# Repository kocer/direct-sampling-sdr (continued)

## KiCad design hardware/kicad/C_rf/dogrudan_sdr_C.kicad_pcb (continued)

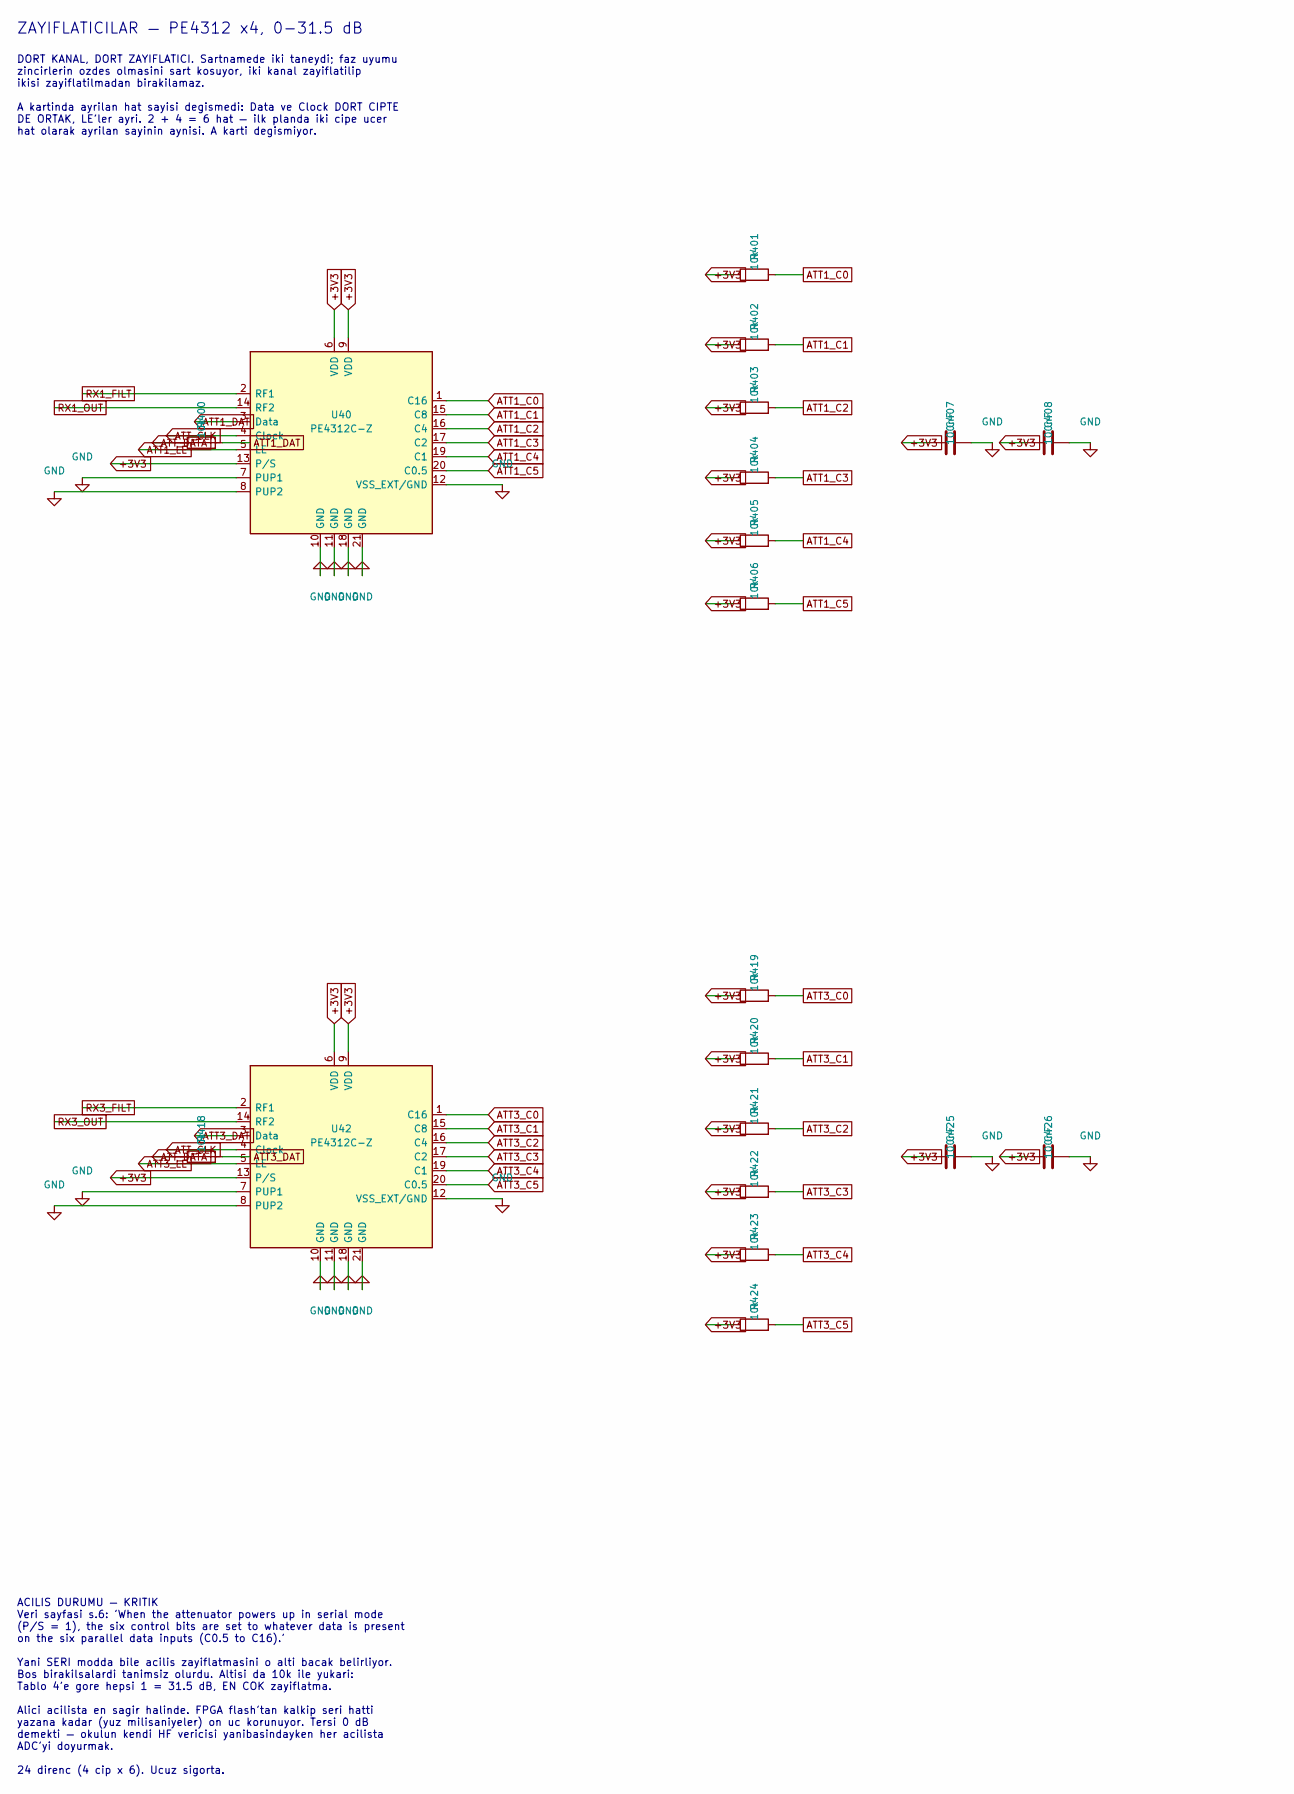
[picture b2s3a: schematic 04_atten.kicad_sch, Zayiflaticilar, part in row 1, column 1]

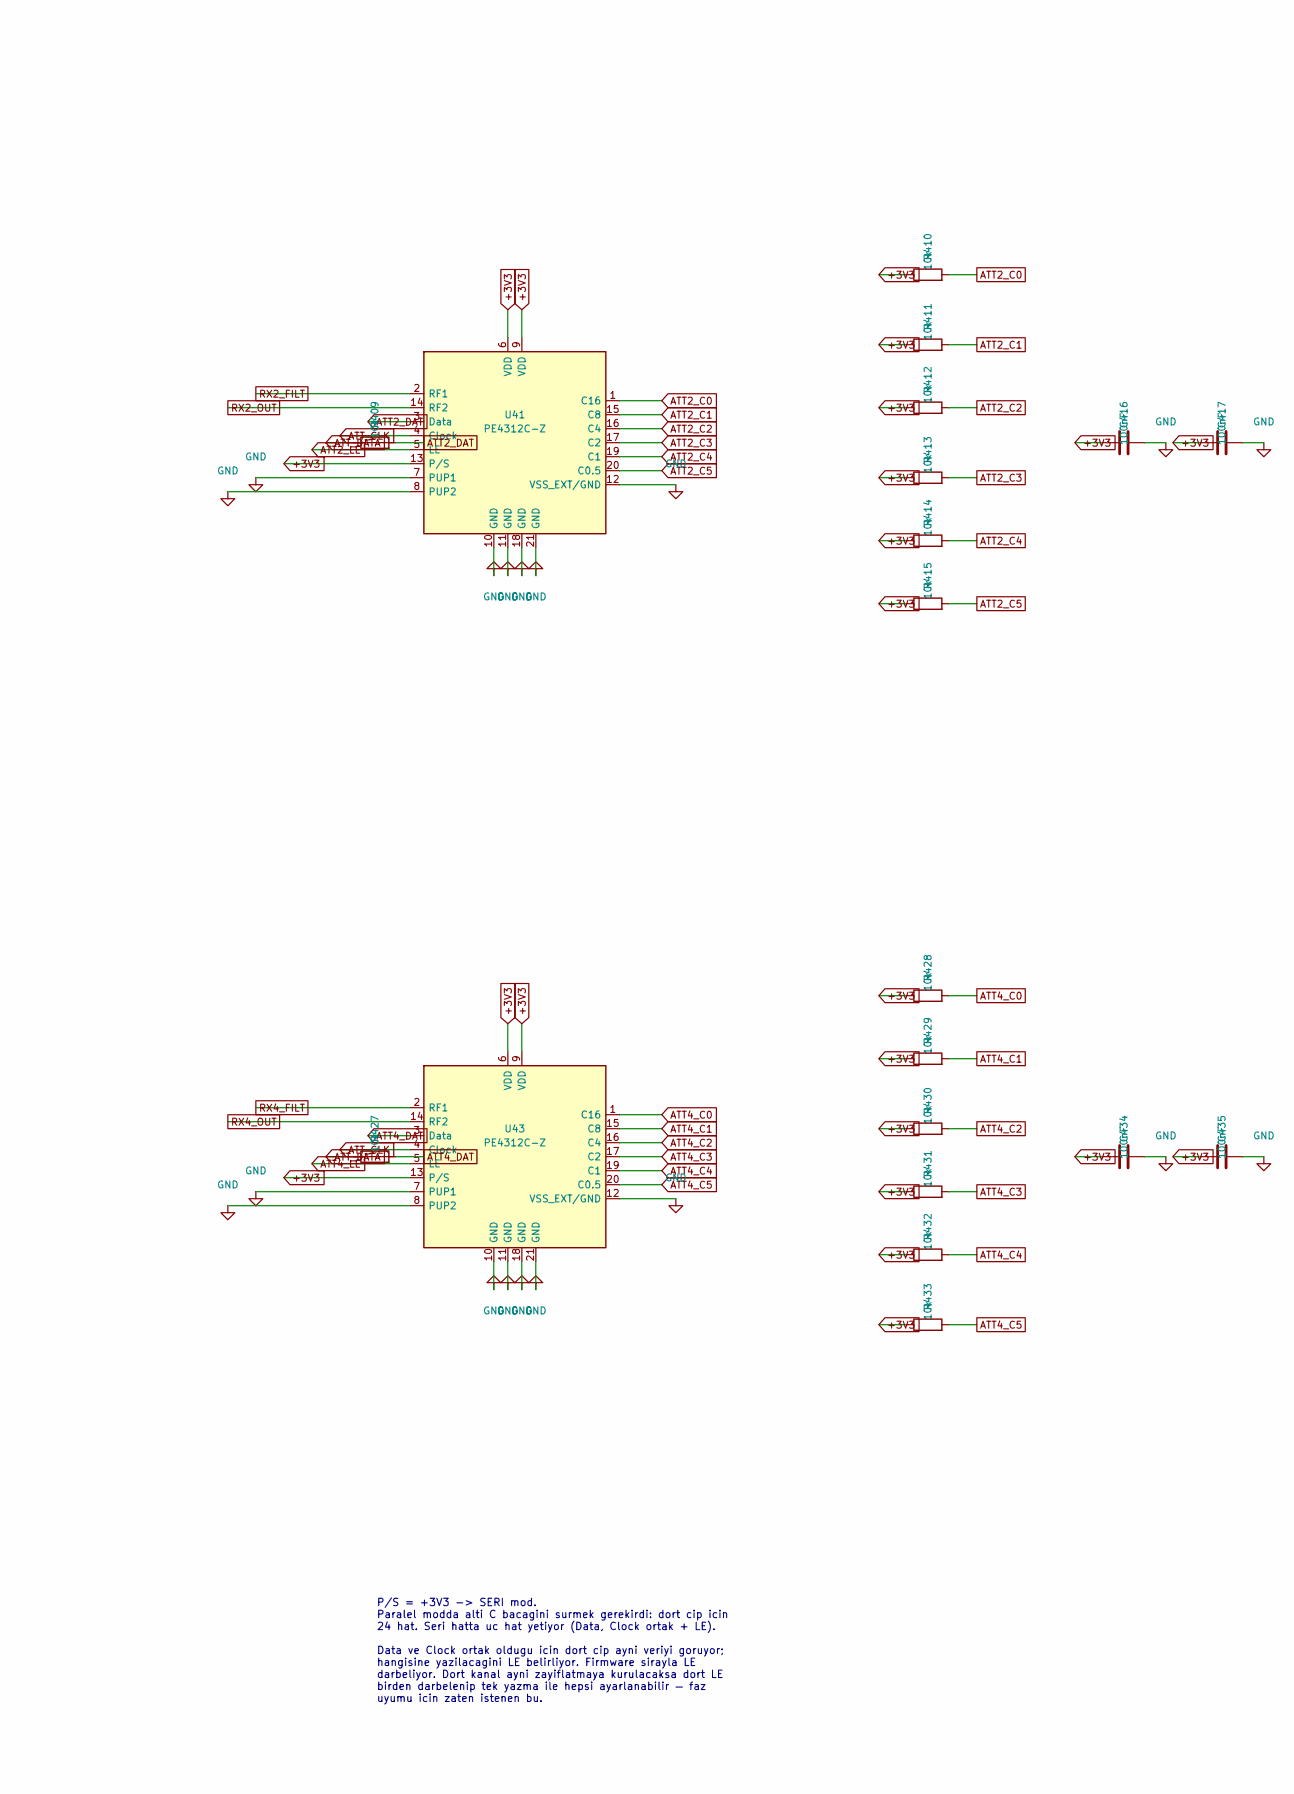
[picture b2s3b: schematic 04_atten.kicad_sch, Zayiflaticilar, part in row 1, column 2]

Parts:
C407, C408, C416, C417, C425, C426, C434, C435: 100nF; C_0402_1005Metric
R400, R401, R402, R403, R404, R405, R406, R409, R410, R411, R412, R413, R414, R415, R418, R419, R420, R421, R422, R423, R424, R427, R428, R429, R430, R431, R432, R433: 10k; R_0603_1608Metric
U40, U41, U42, U43: PE4312C-Z; TQFN-20-1EP_4x4mm_P0.5mm_EP2.1x2.1mm

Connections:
+3V3: C407.1, C408.1, C416.1, C417.1, C425.1, C426.1, C434.1, C435.1, R401.1, R402.1, R403.1, R404.1, R405.1, R406.1, R410.1, R411.1, R412.1, R413.1, R414.1, R415.1, R419.1, R420.1, R421.1, R422.1, R423.1, R424.1, R428.1, R429.1, R430.1, R431.1, R432.1, R433.1, U40.6 (VDD), U40.9 (VDD), U40.13 (P/S), U41.6 (VDD), U41.9 (VDD), U41.13 (P/S), U42.6 (VDD), U42.9 (VDD), U42.13 (P/S), U43.6 (VDD), U43.9 (VDD), U43.13 (P/S); also elsewhere on the board
ATT1_C0: R401.2, U40.1 (C16)
ATT1_C1: R402.2, U40.15 (C8)
ATT1_C2: R403.2, U40.16 (C4)
ATT1_C3: R404.2, U40.17 (C2)
ATT1_C4: R405.2, U40.19 (C1)
ATT1_C5: R406.2, U40.20 (C0.5)
ATT1_DAT: R400.2, U40.3 (Data)
ATT1_LE: U40.5 (LE); also elsewhere on the board
ATT2_C0: R410.2, U41.1 (C16)
ATT2_C1: R411.2, U41.15 (C8)
ATT2_C2: R412.2, U41.16 (C4)
ATT2_C3: R413.2, U41.17 (C2)
ATT2_C4: R414.2, U41.19 (C1)
ATT2_C5: R415.2, U41.20 (C0.5)
ATT2_DAT: R409.2, U41.3 (Data)
ATT2_LE: U41.5 (LE); also elsewhere on the board
ATT3_C0: R419.2, U42.1 (C16)
ATT3_C1: R420.2, U42.15 (C8)
ATT3_C2: R421.2, U42.16 (C4)
ATT3_C3: R422.2, U42.17 (C2)
ATT3_C4: R423.2, U42.19 (C1)
ATT3_C5: R424.2, U42.20 (C0.5)
ATT3_DAT: R418.2, U42.3 (Data)
ATT3_LE: U42.5 (LE); also elsewhere on the board
ATT4_C0: R428.2, U43.1 (C16)
ATT4_C1: R429.2, U43.15 (C8)
ATT4_C2: R430.2, U43.16 (C4)
ATT4_C3: R431.2, U43.17 (C2)
ATT4_C4: R432.2, U43.19 (C1)
ATT4_C5: R433.2, U43.20 (C0.5)
ATT4_DAT: R427.2, U43.3 (Data)
ATT4_LE: U43.5 (LE); also elsewhere on the board
ATT_CLK: U40.4 (Clock), U41.4 (Clock), U42.4 (Clock), U43.4 (Clock); also elsewhere on the board
ATT_DATA: R400.1, R409.1, R418.1, R427.1; also elsewhere on the board
RX1_FILT: U40.2 (RF1); also elsewhere on the board
RX1_OUT: U40.14 (RF2); also elsewhere on the board
RX2_FILT: U41.2 (RF1); also elsewhere on the board
RX2_OUT: U41.14 (RF2); also elsewhere on the board
RX3_FILT: U42.2 (RF1); also elsewhere on the board
RX3_OUT: U42.14 (RF2); also elsewhere on the board
RX4_FILT: U43.2 (RF1); also elsewhere on the board
RX4_OUT: U43.14 (RF2); also elsewhere on the board

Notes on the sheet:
ZAYIFLATICILAR — PE4312 x4, 0-31.5 dB
P/S = +3V3 -> SERI mod. Paralel modda alti C bacagini surmek gerekirdi: dort cip icin 24 hat. Seri hatta uc hat yetiyor (Data, Clock ortak + LE). Data ve Clock ortak oldugu icin dort cip ayni veriyi goruyor; hangisine yazilacagini LE belirliyor. Firmware sirayla LE darbeliyor. Dort kanal ayni zayif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
ACILIS DURUMU — KRITIK Veri sayfasi s.6: 'When the attenuator powers up in serial mode (P/S = 1), the six control bits are set to whatever data is present on the six parallel data inputs (C0.5 to C16).' Yani SERI modda bile acilis zayiflatmasini o alti bacak belirliyor. Bos birakilsalardi tanimsiz 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
DORT KANAL, DORT ZAYIFLATICI. Sartnamede iki taneydi; faz uyumu zincirlerin ozdes olmasini sart kosuyor, iki kanal zayiflatilip ikisi zayiflatilmadan birakilamaz. A kartinda ayrilan hat sayisi degismedi: Data ve Clock DORT CIPTE DE ORTAK, LE'ler ayri. 2 + 4 = 6 hat — ilk planda iki cipe ucer hat ol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

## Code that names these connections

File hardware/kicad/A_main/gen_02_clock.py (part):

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# ================================================================== VCXO
s.text("VCXO — ABLNO-V, 80.000 MHz", 16, 40, 1.6)
s.sym(X, "Y10", "ABLNO-V-80.000MHZ", 55, 70, fp=FX)
s.pin_label(X, "1", 55, 70, 0, "VCXO_VC", "input", d=10.16)
s.pin_label(X, "4", 55, 70, 0, "VCXO_VDD", "input", d=10.16)
s.pin_label(X, "3", 55, 70, 0, "CLK80", "output", d=10.16)
s.pin_power(X, "2", 55, 70, 0, "GND", d=7.62)
# VCXO beslemesi ferritten geciyor, ferrit pasif: ERC bu rayda bir
# guc kaynagi goremiyor. Bayrak, gercek baglanti degil.
s.glabel("VCXO_VDD", 30, 40, "input")
s.wire(30, 40, 30, 33.65)
s.pwr_flag(30, 33.65)

# ferrit + ayristirma: besleme gurultusu DOGRUDAN faz gurultusu
s.sym(L, "FB10", "ferrit 600R", 55, 40, rot=90, fp=FFB)
s.pin_label(L, "1", 55, 40, 90, "+3V3_CLK", "input")
s.pin_label(L, "2", 55, 40, 90, "VCXO_VDD", "output")
for i, v in enumerate(("100nF", "10uF")):
    s.sym(C, cnt("C"), v, 95 + i * 20, 45, rot=90, fp=FC)
    s.pin_label(C, "1", 95 + i * 20, 45, 90, "VCXO_VDD", "passive")
    s.pin_power(C, "2", 95 + i * 20, 45, 90, "GND")

s.text("Besleme gurultusu DOGRUDAN faz gurultusune donusuyor.\\n"
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
# 3.3 V CMOS cikisi 1.8 V p-p sinira indiriliyor
s.sym(R, "R210", "220R", 60, 145, rot=90, fp=FR)
s.pin_label(R, "1", 60, 145, 90, "CLK80", "passive")
s.pin_label(R, "2", 60, 145, 90, "CLK80_DIV", "passive")
s.sym(R, "R211", "100R", 85, 158, rot=90, fp=FR)
s.pin_label(R, "1", 85, 158, 90, "CLK80_DIV", "passive")
s.pin_power(R, "2", 85, 158, 90, "GND")

s.sym(C, "C210", "100nF", 110, 145, rot=90, fp=FC)
s.pin_label(C, "1", 110, 145, 90, "CLK80_DIV", "passive")
s.pin_label(C, "2", 110, 145, 90, "BUFCLK_P", "passive")
s.sym(C, "C211", "100nF", 110, 170, rot=90, fp=FC)
s.pin_label(C, "1", 110, 170, 90, "BUFCLK_N", "passive")
s.pin_power(C, "2", 110, 170, 90, "GND")

# her iki giris VREF'e (VS/2 = 0.9 V) 1k ile bias
for i, net in enumerate(("BUFCLK_P", "BUFCLK_N")):
    s.sym(R, f"R{212 + i}", "1k", 145, 145 + i * 25, rot=90, fp=FR)
    s.pin_label(R, "1", 145, 145 + i * 25, 90, "CLK_VREF", "passive")
    s.pin_label(R, "2", 145, 145 + i * 25, 90, net, "passive")
s.sym(C, "C212", "100nF", 175, 158, rot=90, fp=FC)
s.pin_label(C, "1", 175, 158, 90, "CLK_VREF", "passive")
s.pin_power(C, "2", 175, 158, 90, "GND")

s.text("** BU BOLUM ILK PLANDA YOKTU. ** VCXO cikisi 3.3 V LVCMOS,\\n"
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s.text("ADCLK846 — 1:6 LVDS", 300, 40, 2.0)
BX, BY = 340, 110
s.sym(B, "U15", "ADCLK846BCPZ", BX, BY, fp=FB, unit=1)
s.pin_label(B, "3", BX, BY, 0, "BUFCLK_P", "input", d=10.16)
s.pin_label(B, "2", BX, BY, 0, "BUFCLK_N", "input", d=15.24)
s.pin_label(B, "1", BX, BY, 0, "CLK_VREF", "output", d=20.32)
s.pin_power(B, "5", BX, BY, 0, "GND", d=25.4)      # CTRL_A = 0 -> LVDS
s.pin_power(B, "6", BX, BY, 0, "GND", d=30.48)     # CTRL_B = 0 -> LVDS
s.pin_power(B, "7", BX, BY, 0, "GND", d=35.56)     # SLEEP = 0 -> normal
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    s.pin_label(R, "1", 320 + i * 40, 215, 90, f"{net}_P", "passive")
    s.pin_label(R, "2", 320 + i * 40, 215, 90, f"{net}_N", "passive")
s.sym(R, "R222", "100R", 400, 215, rot=90, fp=FR)
s.pin_label(R, "1", 400, 215, 90, "FPGA_PCLK_P", "passive")
s.pin_label(R, "2", 400, 215, 90, "FPGA_PCLK_N", "passive")

s.text("Her LVDS ciftinin ucunda 100R sonlandirma, ALICIYA yakin.\\n"
       "AD9251 saat girisi PECL/LVDS/1.8V CMOS kabul ediyor (Rev.C),\\n"
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       "Neden FPGA'dan uretmedik: FPGA cikis jitter'i ps mertebesinde,\\n"
       "verilen sinyalin faz gurultusune dogrudan giriyor. 36 kurusluk\\n"
       "parca TX spektrumunu kurtariyor.\\n\\n"
       "DAC1_CLK cipin hem CLK1 hem CLK2 bacagina gidiyor (cift port,\\n"
       "iki kanal ayni saatte). DAC2 interleaved, tek IQCLK.",
       16, 355, 1.3)

# ================================================================== test
s.text("TEST NOKTASI", 300, 335, 1.6)
s.sym(R, "R230", "100R", 320, 350, rot=90, fp=FR)
s.pin_label(R, "1", 320, 350, 90, "CLKTEST_P", "passive")
s.pin_label(R, "2", 320, 350, 90, "CLKTEST_N", "passive")
s.text("Alti numarali cikis test icin sonlandirilmis. Bringup'ta\\n"
       "osiloskopla saatin gercekten 80 MHz oldugu buradan gorulur —\\n"
       "TASARIM.md §11 adim 2. Kart kenarina iki pad.", 300, 358, 1.3)
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
# ================================================================== FPGA saati
# FPGA'YA HIC SAAT GIRMIYORDU.
# ADCLK846'nin FPGA'ya ayrilan cikisi (pin 18/17 -> FPGA_PCLK_P/N)
# 100R sonlandirmaya (R222) gidip BITIYORDU: agin uclari yalnizca
# R222 ve U15'ti, U10 hic yoktu. NETLIST.md §2 niyeti yazmis ama
# baglanti cizilmemis.
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s.text("FPGA SAATI — LVDS -> 3.3 V CMOS", 16, 400, 2.0)
FX, FY = 60, 435
s.sym(LV, "U18", "SN65LVDS2DBVR", FX, FY, fp=FLV)
s.pin_label(LV, "3", FX, FY, 0, "FPGA_PCLK_P", "input", d=10.16)
s.pin_label(LV, "4", FX, FY, 0, "FPGA_PCLK_N", "input", d=15.24)
s.pin_label(LV, "5", FX, FY, 0, "FPGA_CLK80", "output", d=10.16)
s.pin_label(LV, "1", FX, FY, 0, "+3V3", "input", d=15.24)
s.pin_power(LV, "2", FX, FY, 0, "GND", d=7.62)
s.sym(C, cnt("C"), "100nF", FX + 35, FY, rot=90, fp=FC)
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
